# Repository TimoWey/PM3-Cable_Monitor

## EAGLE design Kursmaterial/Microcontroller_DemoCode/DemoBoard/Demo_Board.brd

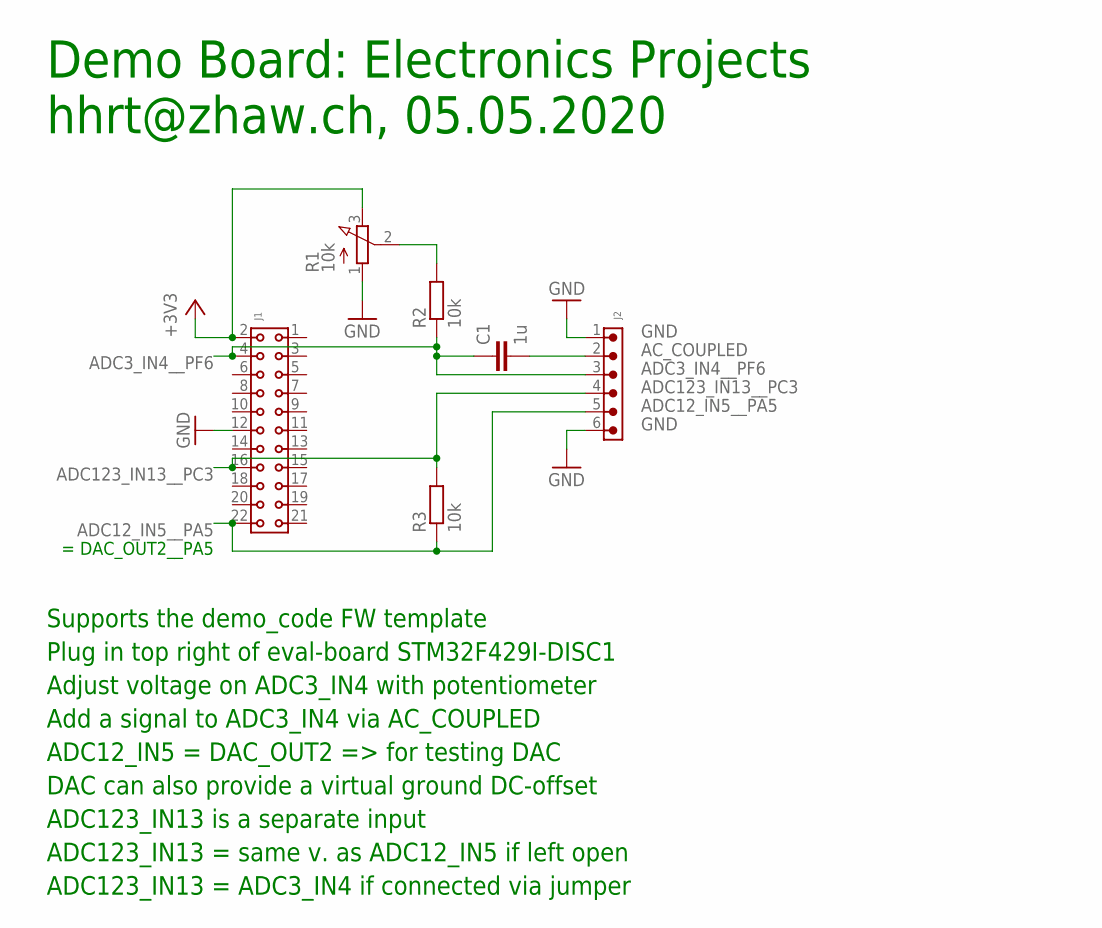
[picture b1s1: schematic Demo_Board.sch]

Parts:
C1: 1u; C0805
J1: 6130XX21821_61302221821; 61302221821
J2: 6130XX11121_61300611121; 61300611121
R1: 10k; EVUF
R2, R3: 10k; R0805

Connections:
+3V3: J1.2, R1.3 (E)
AC_COUPLED: C1.2, J2.2
ADC3_IN4__PF6: C1.1, J1.4, J2.3, R2.1
ADC12_IN5__PA5: J1.22, J2.5, R3.1
ADC123_IN13__PC3: J1.16, J2.4, R3.2
GND: J1.12, J2.1, J2.6, R1.1 (A)
unnamed: R1.2 (S), R2.2

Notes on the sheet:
Demo Board: Electronics Projects hhrt@zhaw.ch, 05.05.2020
= DAC_OUT2__PA5
Supports the demo_code FW template Plug in top right of eval-board STM32F429I-DISC1 Adjust voltage on ADC3_IN4 with potentiometer Add a signal to ADC3_IN4 via AC_COUPLED ADC12_IN5 = DAC_OUT2 => for testing DAC DAC can also provide a virtual ground DC-offset ADC123_IN13 is a separate input ADC123_IN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

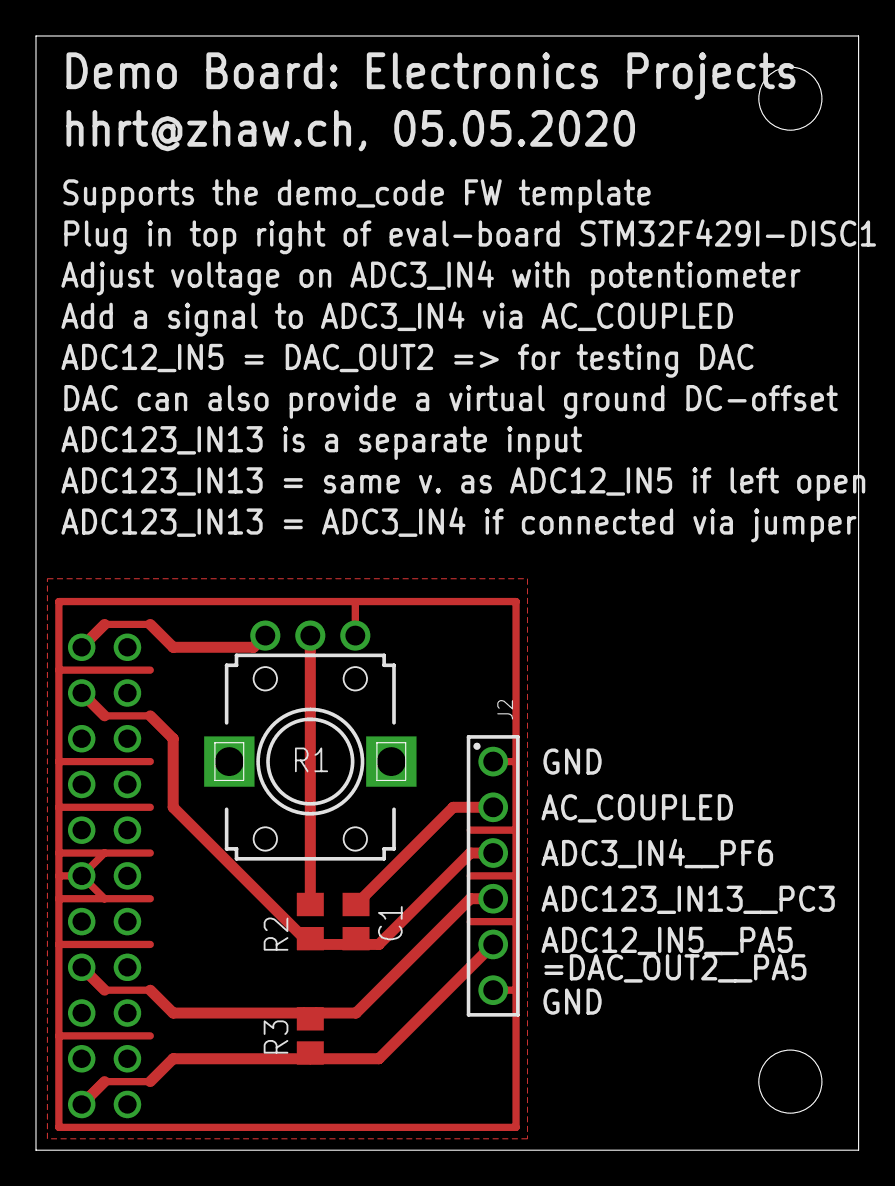
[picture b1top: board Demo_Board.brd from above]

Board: 2 copper layers, 45.7 x 61.9 mm, 6 parts (1 on the bottom side), 7 nets.

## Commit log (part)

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2023-10-13 software gugus
2023-10-13 Final Design Done
2023-10-13 Done with PCB Design V1.0
2023-10-20 3d files
2023-10-20 report fertig
2023-10-20 Bom und Image
2023-10-20 BOM usw
2023-10-23 mööööh
2023-10-23 saftig
2023-10-23 abstract done and gitignore
2023-10-23 introduction finished
2023-10-23 introduction added and finished, specification added WIP
2023-10-23 crazy pics
2023-10-23 dupps duppa gantttttttttttttttt
2023-10-23 Push
2023-10-25 calculation
2023-10-25 pushi
2023-10-27 korrigierter text vom Mat TOP G
2023-10-27 LOLOLO
2023-10-28 pushi kurac
2023-11-02 Backup Schematics
2023-11-02 ladlosas
2023-11-02 Schema für Messung
2023-11-02 suppa code geshriben
2023-11-02 Unbennent
2023-11-03 Load Switch code fix
2023-11-03 Schematics Update and measurement Demo
2023-11-03 gitignore
2023-11-10 simulation matlab und spice
2023-11-11 messungen
2023-11-11 bilder gantt etc
2023-11-12 HW report done
2023-11-17 Amp Detection Script
2023-11-17 Set up project
2023-11-17 started implementing the menu switchcase
2023-11-24 Branchy
2023-11-24 gugus
2023-11-24 copypasta
2023-11-24 GPIO
2023-11-24 Revert "Branchy"
    This reverts commit 4ddf2e682ee2b218aa63f2b84ef7dd3e2dd7838d.
2023-11-24 Revert "Branchy"
    This reverts commit 77043ae8ee52b0a20f0d0a708fc1d9c6624f671d.
2023-11-24 Grundgerüst
2023-11-24 fortschritt switch case
2023-11-26 gitignore update
2023-11-26 somewhat working state machine(GUI)
2023-11-26 state maschine progress
2023-11-28 state machine basics done
2023-11-29 vscode debugging
2023-11-30 vs code annoying
2023-12-01 touchGFX project init
2023-12-01 first menu done
2023-12-01 basic menu done, code generated
2023-12-01 GUI progress
2023-12-02 Branchie
2023-12-02 Yolo
2023-12-02 on off button
2023-12-02 pins for on off defined in mx
2023-12-03 power led working, pe13 set high
    device can be powered on with the button on the extender board, in init function the PE5 is set to high. also PE13 is set to high indicating device ON
2023-12-03 device can be turned off via button
    implemented ISR for button on sub print... device wil turn off when pressed for atleast 200ms
2023-12-03 added shutdown screen and shutdown touch button is wokring
    added windows shutdown screen when shutoff button is pressed. also PE5 is pulled low when shutoff button is pressed on the screen
2023-12-04 played around with gauge layout and displaying current etc
2023-12-04 adjustments
2023-12-04 hearthbeat and timeout
    1 second heartbeat implemented on userled and screentimout to 60 seconds. touch reset must be implemented
2023-12-04 sleep timout progress
    almost done with displaying the value on the gui
2023-12-04 presenter progress
2023-12-04 Measurement Setup for Presentation
    Outputs Raw Value of peaks, frequency and plots all ADC Channels
2023-12-04 Done visualitation
2023-12-05 gauge display value workd
    i was able to display the timeout value on the temporary gauge in main view
2023-12-05 displaying timout on GUI works
    displaying the timout value on the GUI works, included hearthbeat in FREERTOS task -> removed TIM7 since its useless now
2023-12-05 timeout reset when touched + transition added
    finally the timeout is being reset to 60 when the display is touched, also a shutdown transition was added when the timeout runs out
2023-12-05 fixed all nasty code -> simulation is again possible in parallel
    used #ifndef SIMULATION so differentiate between IDE and sumulation
2023-12-05 gui progress
    implemented both single and accurate menus completely
2023-12-05 small fixed, second screen with timeout implement
    added the sleep timeout to the second sreen as test, some small fixed
2023-12-06 timeout function now displayed in info menu aswell
2023-12-06 timeout added to menus
    now all relevant menus show the timeout
2023-12-06 added calibration_pad menu
    added another calibration pad menu and fixed some text issues
2023-12-06 hall menu added
    added last menu for hall sensor calibration
2023-12-07 Testing
2023-12-08 PUSH CAP
2023-12-08 include verhengt huso
2023-12-08 Buggy Woogie Demo Ready
2023-12-08 Presentation Ready
2023-12-08 displaying values through callback
    trying to display a placeholder value through callback method
2023-12-08 displaying values works
    now voltage, current frequency and the angle on the gauge can be displayed with a callback
2023-12-08 working, pro .c import
2023-12-08 Signal Strength and Main Frequency Function added
    Edited the main_frequency function to allow us to calculate the signal strenght.
    Added Struct to call and get the necessary values easily -> Code more readable
    @todo
    Find out how calibration is done -> enable to calculate distance and angle
2023-12-08 lib fix
2023-12-08 measureing and claculation inclusion works
2023-12-08 some progress
2023-12-11 some debugging
2023-12-11 bwoken
2023-12-11 debugging
2023-12-11 dma adc debugging
2023-12-12 debugging again
2023-12-12 dubugging disabled tim1-3 and dma2 mx
2023-12-12 super duper code
2023-12-12 typo corrected
2023-12-12 code cleanup
2023-12-12 increased touchgfx tick calling
2023-12-16 gui progress, but display buggy
2023-12-17 added scrolling menu in calubvration pad
2023-12-17 removed unnecessary resources
2023-12-17 flash storing works in last sector
2023-12-18 write values from flash to swipecontainer successful
2023-12-18 deleted unnecessary calibration screens
2023-12-18 deleted hall calibration screen
2023-12-18 overwrite flash values from gui works
2023-12-18 left pad code advanced
2023-12-18 added hall calibartion menus
2023-12-18 Distance Calculation
2023-12-18 pads flash value works
2023-12-18 all calibration settings work
2023-12-18 TIM14 PWM for Buzzer on PA7
2023-12-18 pwm progress and button image
2023-12-19 Coefficients adapted
2023-12-19 pwm 4khz
2023-12-20 pwm for led setup
2023-12-20 included ale's calculations
2023-12-20 GUI update
2023-12-20 Reworked whole Calculation file
2023-12-20 GUI DONE & PROJECT CLEANUP
2023-12-20 Added whole lotta stuff
2023-12-20 Added Accurate FFT reading -> for Calibration
2023-12-20 updated calibration
2023-12-20 worked on callback for coefficients - WIP
2023-12-21 Added Accurate FFT calculation (used for Calibration)
2023-12-21 callback to coefficient function works
2023-12-21 calc coeff from ale
2023-12-21 distance value cap
2023-12-21 small fixed (timeout) and code cleanup
2023-12-22 typos
2023-12-22 bug fixing
2023-12-22 UPDATO
2023-12-22 Leck mio am arscho
2023-12-22 coeff added
2023-12-23 Current Aprox, needs to be tested
2023-12-23 Filled 3Phase menus and added measurement parameter for single and 3 phase
    Needs to be tested
2023-12-23 Work in Progress
2023-12-23 Push, tests was good habibi
2023-12-23 TouchGFX Updated
2023-12-23 flash erweitert
2023-12-23 load transition fixed
2023-12-23 POSH
2023-12-23 gui toggle added
2023-12-23 settings icon
2023-12-23 settings icon changed
2023-12-23 white settings icon
2023-12-23 new settings icon added
2023-12-25 PWM implemented with toggle button menu
2023-12-25 Current Calculation optimized
2023-12-25 Added Error Testing and Outputting to calculation.c
2023-12-25 Added Error Detection and Implemented the output of the error on the respective View.cpp file
2023-12-25 Added Error Detection and Outputting of errors
    Changed wildcard so that Einheit isn't being printed from wildcard, sondern from View.cpp float print instead
2023-12-25 pwm for LED works
2023-12-25 Updated Docs headers and added calibration measurement loops
2023-12-25 MASHALLAH
2023-12-25 doxymoxy
2023-12-25 touchgfx included suppa sache
2023-12-25 copilot goes brrrrrrrrrrrrrrrrt
2023-12-26 logo added
2023-12-26 Image ordner
2023-12-26 supi dupi yippue ayeeey
2023-12-26 mainpage imporovementsssssssssss
2023-12-26 Grafike
2023-12-26 testing edited
2023-12-26 testing witer
2023-12-26 GRAPH VIZ
2023-12-26 PUSHI KURAC
    Done mit Calculation und Measuring c dokumentierung
2023-12-27 fixed flash issue
2023-12-27 pushii
2023-12-27 testing continued, bug in accurate meas
2023-12-27 testing and main.c comments
2023-12-27 almost done
2023-12-27 I guess its kinda done
2023-12-27 Push Main screen plus GUI Funktione Doku
2023-12-27 logo2
2023-12-27 Last Push (hopefully)
2023-12-27 Sorry last push

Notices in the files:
parts and their libraries:
Wurth_Connectors_WR-PHD: Copyright: Würth Elektronik
